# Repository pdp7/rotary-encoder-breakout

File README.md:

# Rotary Encoder breakout with pull-ups
Breakout board designed in [KiCad](http://kicad.org/) makes it easy to put a rotary encoder on a breadboard.  Footprints on the back are meant for [1206 SMD resistors](https://smile.amazon.com/gp/product/B00ZT7QYRM/ref=oh_aui_detailpage_o07_s00).  I choose 1K resistors (marked `102`) when I assembled this board.  

## Blog post
* [Rotary Encoder breakout with pull-ups](https://blog.oshpark.com/2017/04/05/rotary-encoder-breakout-with-pull-up-resistors/)

## Component and Footprint
Using Kicad symbol and footprint by mcous for sparkfun rotary encoder:
  * [mcous/kicad-lib.git](https://github.com/mcous/kicad-lib.git)

## Verified to work
* [SparkFun Rotary Encoder (COM-09117)](https://www.sparkfun.com/products/9117)
  * [Alpha 318-ENC130175F-12PS datasheet](http://www.sparkfun.com/datasheets/Components/TW-700198.pdf)
* [Bourns PEC12R-4220F-S0024-ND (DigiKey)](https://www.digikey.com/product-detail/en/bourns-inc/PEC12R-4220F-S0024/PEC12R-4220F-S0024-ND/4499653)
  * [PEC12R series datasheet](http://www.bourns.com/docs/Product-Datasheets/PEC12R.pdf)

## OSH Park Shared Project
* [Rotary Encoder Breakout with Pull-ups](https://oshpark.com/shared_projects/CN5gjITG)

## Photos
* [Images in GitHub repo](https://github.com/pdp7/rotary-encoder-breakout/tree/master/images)
* [Google Photos gallery](https://photos.google.com/share/AF1QipOhX9UX2NgAdQrnjnlDBVHRBlhoTsk-aBTeFElKHJmRJ3jEOubHJSx6yyrtfOxlVQ?key=OVp3QTREUU9oTkdRYWM1ZXNrQ0psRURYdEpvanZR)

## Video
* [Rotary Encoder Breakout Board with Pull-up Resistors](https://www.youtube.com/watch?v=EKscNrjTDD4)

## Source Code
* [Example for Teensy 3.2](https://github.com/pdp7/rotary-encoder-breakout/blob/master/source/rotary-encoder-test.ino)

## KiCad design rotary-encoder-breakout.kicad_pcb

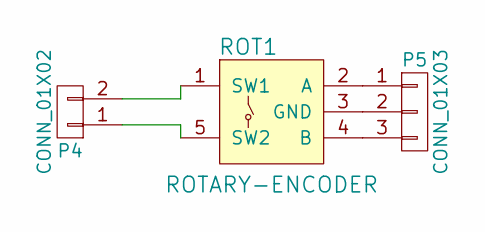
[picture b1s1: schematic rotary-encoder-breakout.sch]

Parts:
P4: CONN_01X02; Pin_Header_Straight_1x02
P5: CONN_01X03; Pin_Header_Straight_1x03
ROT1: ROTARY-ENCODER; SF-ROTARY-ENCODER

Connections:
unnamed: P4.1, ROT1.5 (SW2)
unnamed: P4.2, ROT1.1 (SW1)
unnamed: P5.1, ROT1.2 (A)
unnamed: P5.2, ROT1.3 (GND)
unnamed: P5.3, ROT1.4 (B)

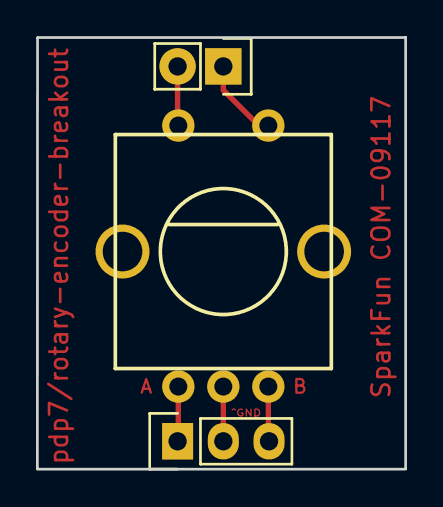
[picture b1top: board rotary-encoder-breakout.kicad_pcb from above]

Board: 2 copper layers, 20.5 x 24.0 mm, 3 parts (0 on the bottom side), 5 nets.

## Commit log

2017-01-17 Initial schematic and layout of rotary-encoder-breakout
2017-01-17 update layout
2017-02-01 Fix schematic and layout so traces are straight to header
2017-02-01 reduce board dimensions to better fit on breadboard
2017-02-01 update shared project link
2017-02-17 Updated rotary encoder pin label
    Per this pull request:
    Modify the schematic for SparkFun rotary encoder #14
    https://github.com/mcous/kicad-lib/pull/14
    I've renamed GND to C. "GND (C)" was too long.
2017-03-10 create version with pull-up resistors
2017-04-04 add images and example Arduino sketch
2017-04-04 resize images to be smaller
2017-04-04 resize preview images
2021-11-08 Update README.md
    https://forum.kicad.info/t/warning-avoid-all-links-to-kicad-pcb-org-use-kicad-org/31521
